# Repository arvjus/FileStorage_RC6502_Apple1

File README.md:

# FileStorage_RC6502_Apple1

This is a collection of HW / SW to provide file storage capabilty for RC6502 Apple1 Replica.
	
## Main Highlights
	* Uses W25Q64 chip to srore the data
	* Simple File system to keep files structured
	* Supported files: type $06 (regular binary), $F1 (Integer Basic, ProDOS file format)
	* Utility programs to prepare disk images or porsions of FS on regular OS (tested on Linux)			
	
## Status
	Quite stable, I use it on dayly basis
 
## Desired improvements
	* Better error handling. In most cases if user does input error or something unexpected happens in communication, the command is just silently ignored.
 	* Better performance in data transfer. It takes about 3 secs to load 1Kb of data.
 
## Screenshots

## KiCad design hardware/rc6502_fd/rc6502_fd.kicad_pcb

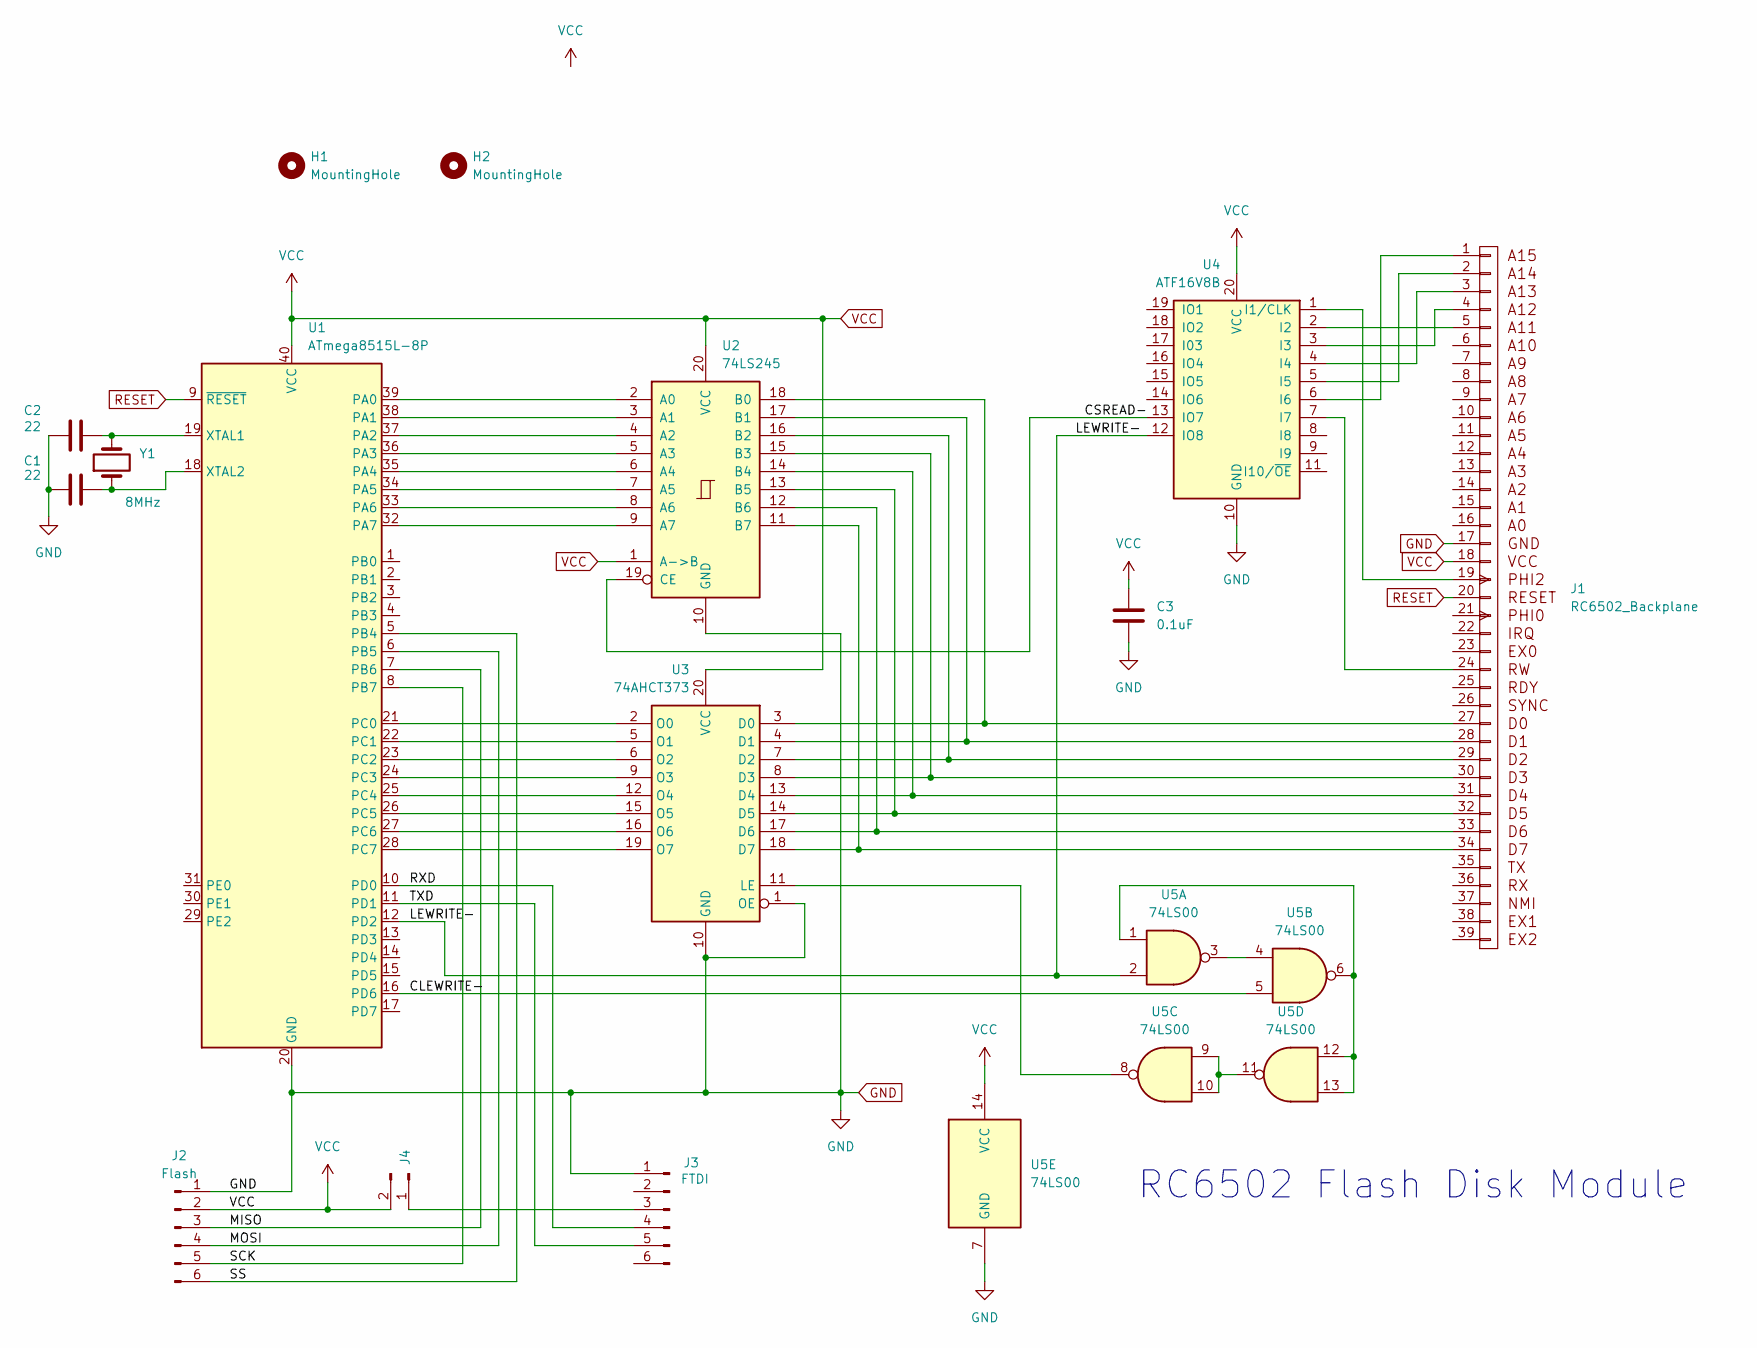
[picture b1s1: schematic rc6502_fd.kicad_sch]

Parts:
C1, C2: 22; C_Disc_D5.0mm_W2.5mm_P2.50mm
C3: 0.1uF; C_Disc_D7.5mm_W5.0mm_P7.50mm
H1, H2: MountingHole; MountingHole_2.5mm
J1: RC6502_Backplane; PinSocket_1x39_P2.54mm_Vertical
J2: Flash; PinHeader_1x06_P2.54mm_Vertical
J3: FTDI; PinSocket_1x06_P2.54mm_Vertical
J4: Conn_01x02_Pin; PinSocket_1x02_P2.54mm_Vertical
U1: ATmega8515L-8P; DIP-40_W15.24mm
U2: 74LS245; DIP-20_W7.62mm
U3: 74AHCT373; DIP-20_W7.62mm
U4: ATF16V8B; DIP-20_W7.62mm
U5: 74LS00; DIP-14_W7.62mm
Y1: 8MHz; Crystal_HC18-U_Vertical

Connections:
/CLEWRITE-: U1.16 (PD6), U5.5
/CSREAD-: U2.19 (CE), U4.13 (IO7)
/LEWRITE-: U1.12 (PD2), U4.12 (IO8), U5.2
/MISO: J2.3, U1.7 (PB6)
/MOSI: J2.4, U1.6 (PB5)
/RXD: J3.4, U1.10 (PD0)
/SCK: J2.5, U1.8 (PB7)
/SS: J2.6, U1.5 (PB4)
/TXD: J3.5, U1.11 (PD1)
GND: C1.1, C2.1, C3.2, J1.17, J2.1, J3.1, U1.20 (GND), U2.10 (GND), U3.1 (OE), U3.10 (GND), U4.10 (GND), U5.7 (GND)
unnamed: J1.5 (A11), U4.2 (I2)
unnamed: J1.4 (A12), U4.3 (I3)
unnamed: J1.3 (A13), U4.4 (I4)
unnamed: J1.2 (A14), U4.5 (I5)
unnamed: J1.1 (A15), U4.6 (I6)
unnamed: J1.27 (D0), U2.18 (B0), U3.3 (D0)
unnamed: J1.28 (D1), U2.17 (B1), U3.4 (D1)
unnamed: J1.29 (D2), U2.16 (B2), U3.7 (D2)
unnamed: J1.30 (D3), U2.15 (B3), U3.8 (D3)
unnamed: J1.31 (D4), U2.14 (B4), U3.13 (D4)
unnamed: J1.32 (D5), U2.13 (B5), U3.14 (D5)
unnamed: J1.33 (D6), U2.12 (B6), U3.17 (D6)
unnamed: J1.34 (D7), U2.11 (B7), U3.18 (D7)
unnamed: J1.19 (PHI2), U4.1 (I1/CLK)
unnamed: J1.24 (RW), U4.7 (I7)
unnamed: J3.3, J4.1
unnamed: U1.39 (PA0), U2.2 (A0)
unnamed: U1.38 (PA1), U2.3 (A1)
unnamed: U1.37 (PA2), U2.4 (A2)
unnamed: U1.36 (PA3), U2.5 (A3)
unnamed: U1.35 (PA4), U2.6 (A4)
unnamed: U1.34 (PA5), U2.7 (A5)
unnamed: U1.33 (PA6), U2.8 (A6)
unnamed: U1.32 (PA7), U2.9 (A7)
unnamed: U1.21 (PC0), U3.2 (O0)
unnamed: U1.22 (PC1), U3.5 (O1)
unnamed: U1.23 (PC2), U3.6 (O2)
unnamed: U1.24 (PC3), U3.9 (O3)
unnamed: U1.25 (PC4), U3.12 (O4)
unnamed: U1.26 (PC5), U3.15 (O5)
unnamed: U1.27 (PC6), U3.16 (O6)
unnamed: U1.28 (PC7), U3.19 (O7)
unnamed: C2.2, U1.19 (XTAL1), Y1.2
unnamed: C1.2, U1.18 (XTAL2), Y1.1
unnamed: U3.11 (LE), U5.8
unnamed: U5.1, U5.6, U5.12, U5.13
unnamed: U5.3, U5.4
unnamed: U5.9, U5.10, U5.11
RESET: J1.20 (RESET), U1.9 (~RESET)
VCC: C3.1, J1.18, J2.2, J4.2, U1.40 (VCC), U2.1 (A->B), U2.20 (VCC), U3.20 (VCC), U4.20 (VCC), U5.14 (VCC)

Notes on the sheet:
RC6502 Flash Disk Module

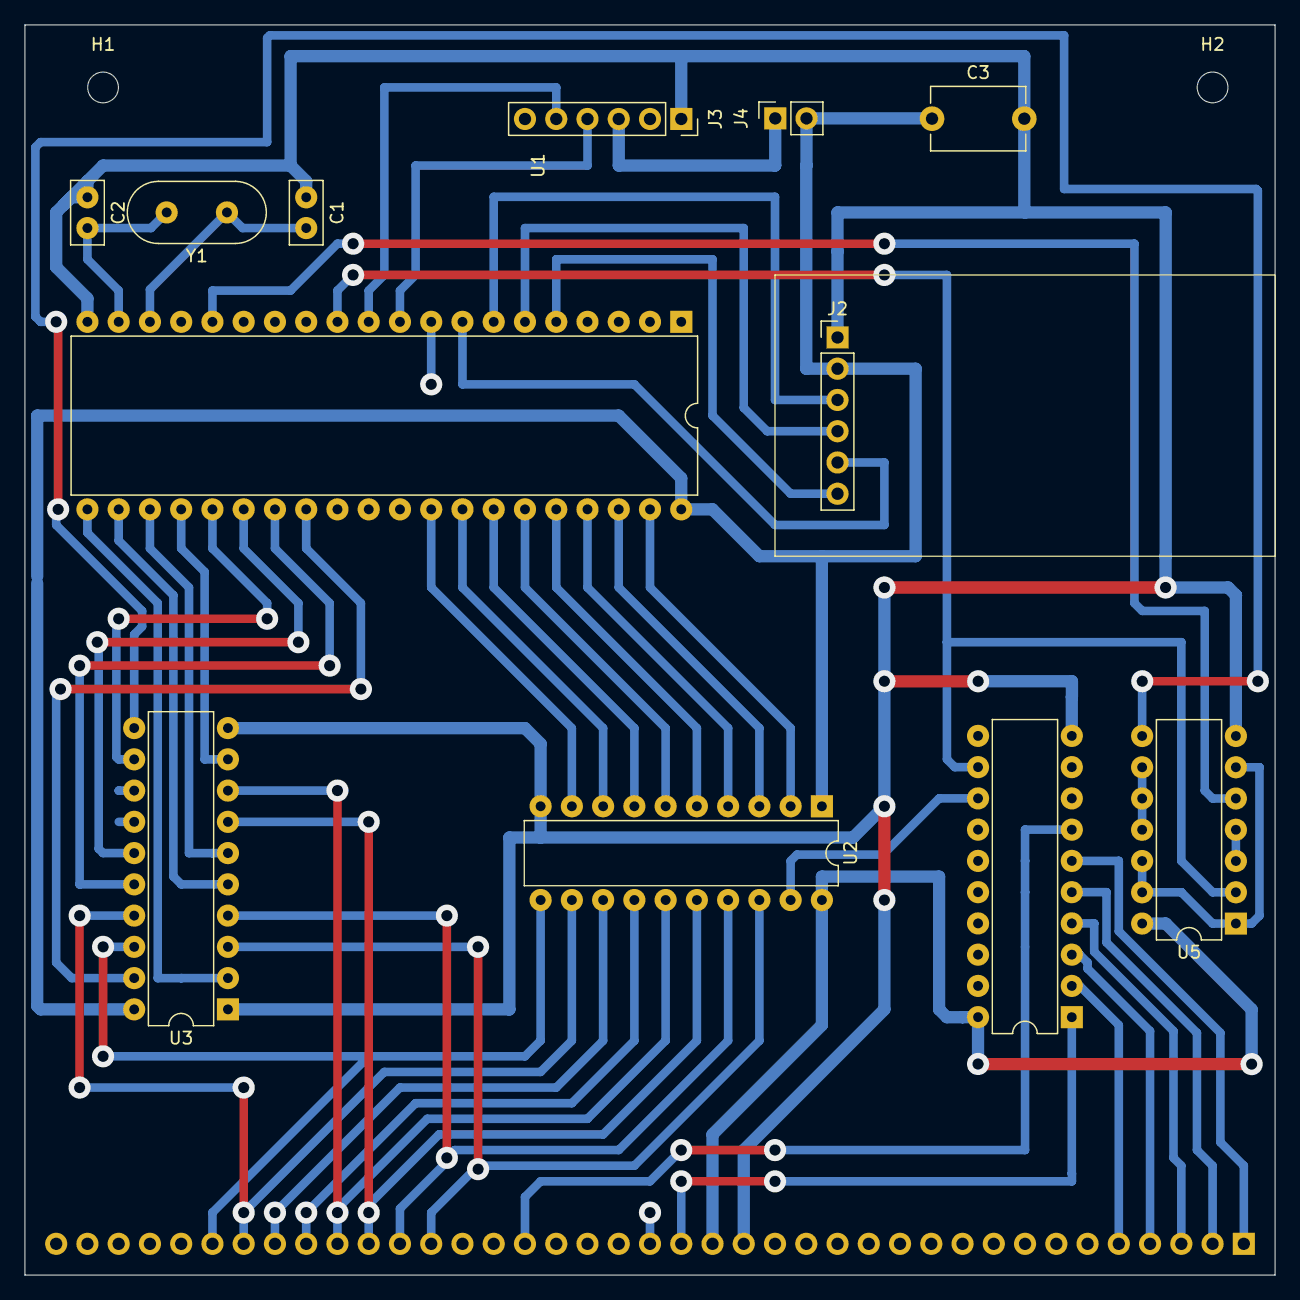
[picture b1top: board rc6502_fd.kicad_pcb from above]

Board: 2 copper layers, 101.6 x 101.6 mm, 15 parts (1 on the bottom side), 50 nets.

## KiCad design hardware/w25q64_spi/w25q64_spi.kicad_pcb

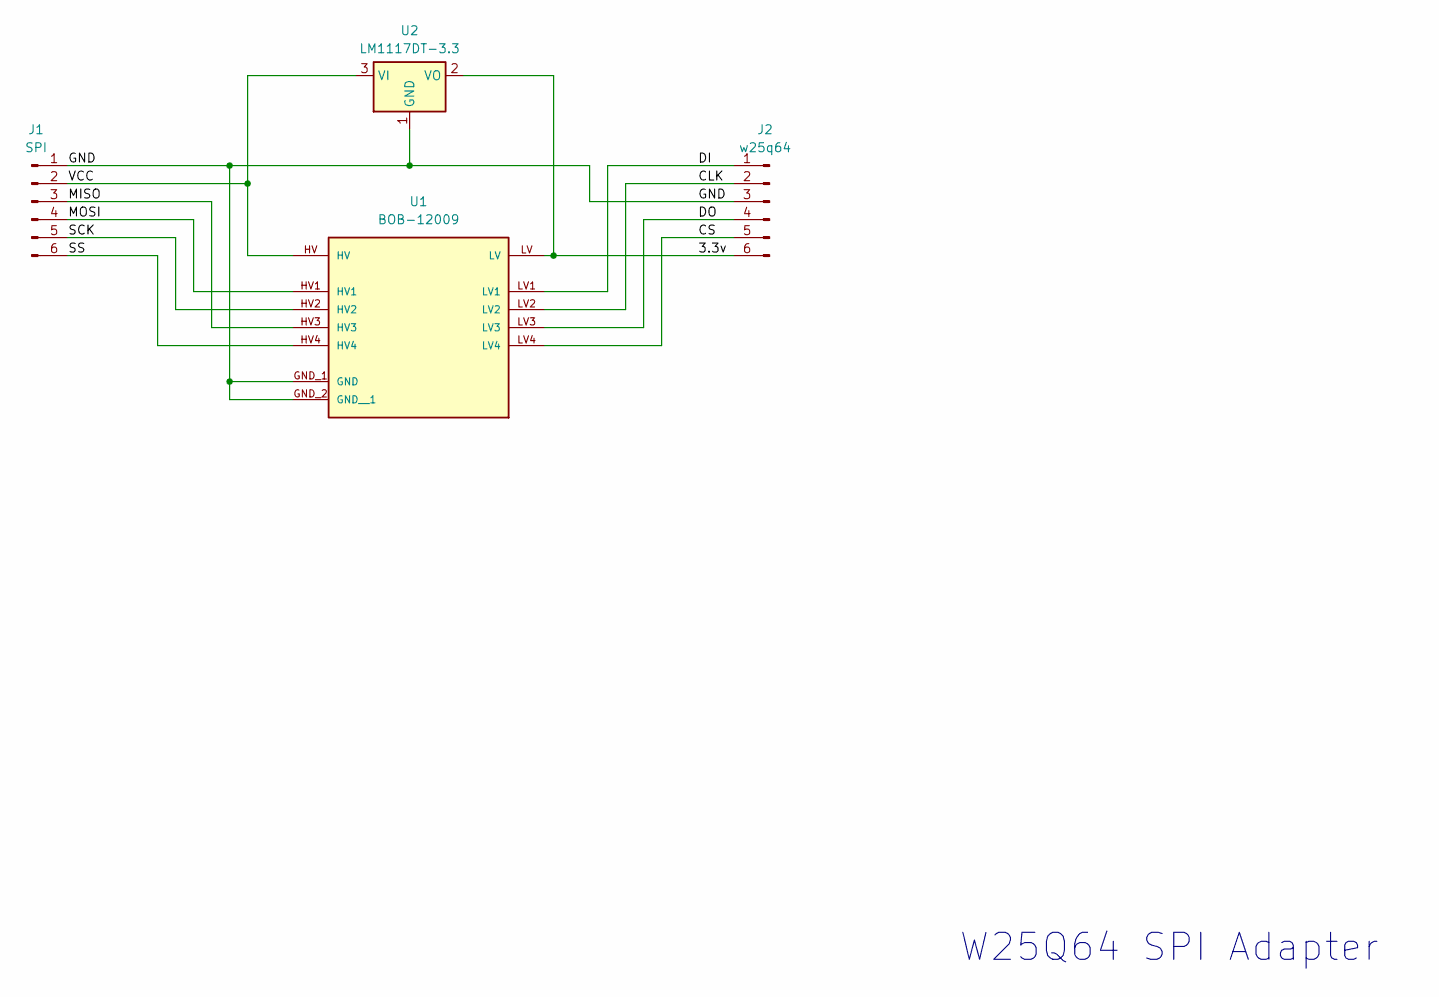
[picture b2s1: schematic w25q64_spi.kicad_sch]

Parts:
J1: SPI; PinSocket_1x06_P2.54mm_Vertical
J2: w25q64; PinSocket_1x06_P2.54mm_Vertical
U1: BOB-12009; CONV_BOB-12009; PARTREV 01
U2: LM1117DT-3.3; TO-252-3_TabPin2

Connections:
/3.3v: J2.6, U1.LV, U2.2 (VO)
/CLK: J2.2, U1.LV2
/CS: J2.5, U1.LV4
/DI: J2.1, U1.LV1
/DO: J2.4, U1.LV3
/GND: J1.1, J2.3, U1.GND_1 (GND), U1.GND_2 (GND__1), U2.1 (GND)
/MISO: J1.3, U1.HV3
/MOSI: J1.4, U1.HV1
/SCK: J1.5, U1.HV2
/SS: J1.6, U1.HV4
/VCC: J1.2, U1.HV, U2.3 (VI)

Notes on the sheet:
W25Q64 SPI Adapter

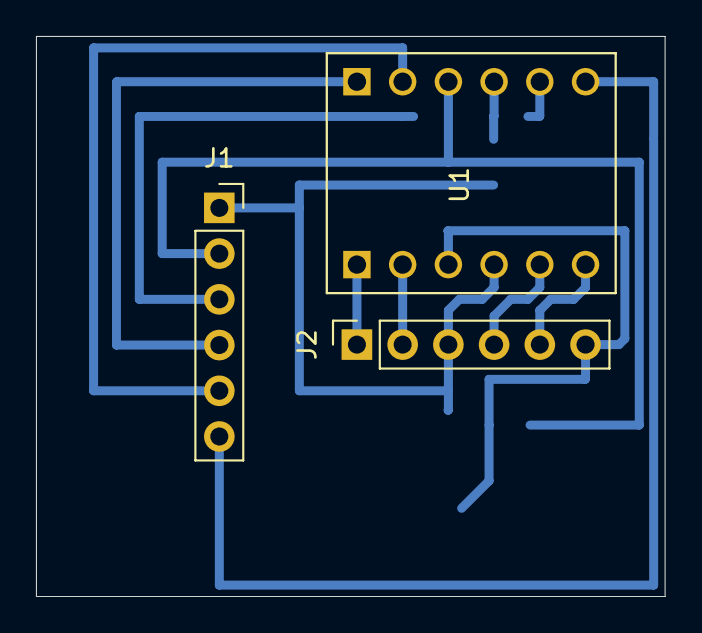
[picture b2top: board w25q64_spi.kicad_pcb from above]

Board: 2 copper layers, 34.9 x 31.1 mm, 4 parts (1 on the bottom side), 11 nets.

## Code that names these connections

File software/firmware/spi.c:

/*
RC6502 FLASH (W25Q64F) Card firmware
Copyright (c) 2025 Arvid Juskaitis
*/

#include "spi.h"

// Function definitions
void SPI_init(uint8_t mode, uint8_t clock_div) {
    // Set MOSI, SCK as Output
    DDRB |= (1 << PB5) | (1 << PB7); // MOSI, SCK
    DDRB &= ~(1 << PB6);             // MISO as Input

    // Enable SPI, Master mode
    SPCR = (1 << SPE) | (1 << MSTR);

    // Set SPI Clock Rate
    SPCR = (SPCR & ~0x03) | (clock_div & 0x03);
    SPSR = (SPSR & ~0x01) | ((clock_div >> 2) & 0x01);

    // Set SPI Mode
    SPCR = (SPCR & ~((1 << CPOL) | (1 << CPHA))) | (mode << CPHA);
}

uint8_t SPI_transfer(uint8_t data) {
    SPDR = data;                      // Load data into the buffer
    while (!(SPSR & (1 << SPIF)));    // Wait until transmission is complete
    return SPDR;                      // Return received data
}

void SPI_setCS(uint8_t cs_pin, uint8_t state) {
    if (state) {
        PORTB |= (1 << cs_pin); // Set CS high
    } else {
        PORTB &= ~(1 << cs_pin); // Set CS low
    }
}

// Define the SPI instance
SPI_t SPI = {
    .init = SPI_init,
    .transfer = SPI_transfer,
    .setCS = SPI_setCS,
};


/*  example usage:

    // Initialize SPI in MODE0, clock divider 4
    SPI.init(SPI_MODE0, SPI_CLOCK_DIV4);

    // Set CS pin as output
    DDRB |= (1 << PB4); // Assuming PB4 is used for CS

    // Communicate with SPI slave
    SPI.setCS(PB4, 0);         // Select slave
    uint8_t received = SPI.transfer(0x55); // Send 0x55 and receive response
    SPI.setCS(PB4, 1);         // Deselect slave

*/

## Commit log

2025-02-12 test
2025-02-12 add project files
2025-02-12 resize images
2025-02-12 Update README.md add links
2025-02-12 removed .DS_Store
2025-02-12 fix copyright text
2025-02-13 handle cd prefix, redesign menu
2025-02-14 update images
2025-02-14 handle BS key in editor
2025-02-18 bugfixes in write operation
2025-02-21 bugfixes, redesign menu, basic support
2025-02-21 readme, screenshot updates
2025-02-24 update screenshots
2025-02-24 add photo
